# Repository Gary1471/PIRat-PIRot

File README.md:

# PIRat & PIRot

Cílem práce je vytvořit funkční prototyp zařízení PIRat a PIRot. PIRat (vysílač) detekuje pomocí PIR senzoru pohyb člověka/zvířete a pošle bezdrátový signál pomocí ESP-NOW zařízení PIRot (přijímač), který zahlásí upozornění o pohybu. PIRat bude mít dva módy, první „skrytý mód“ jen posílá upozornění na PIRot, druhý „normální mód“ pošle upozornění a zároveň sám PIRat upozorní zvukovým znamením. To umožňuje používat zařízení PIRat samostatně bez zařízení PIRot. PIRot bude mít též dva módy, první „skrytý mód“ upozorní uživatele světelným znamením, druhý „normální mód“ upozorní uživatele světelným i zvukovým znamením.

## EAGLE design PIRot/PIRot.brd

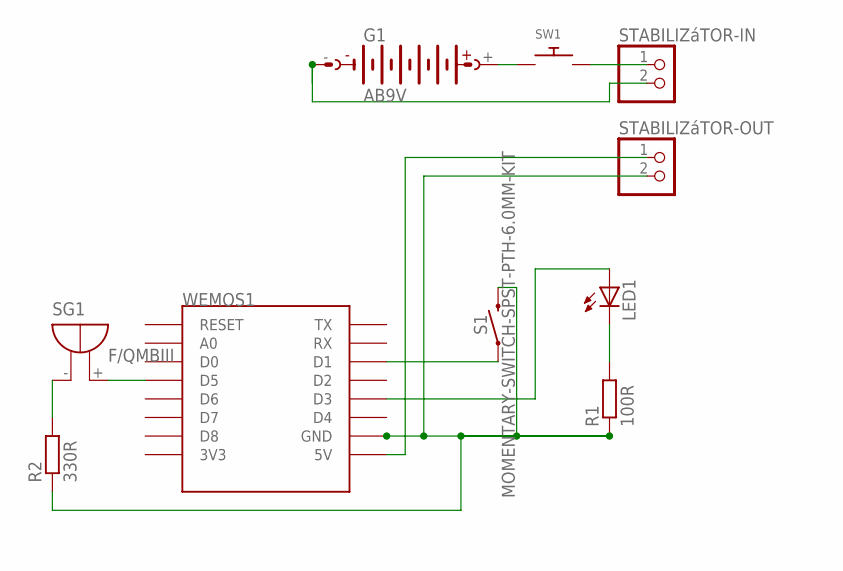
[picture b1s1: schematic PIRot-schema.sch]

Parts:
G1: AB9V
LED1: LED3MM
R1: 100R; 0207/10
R2: 330R; 0207/10
S1: MOMENTARY-SWITCH-SPST-PTH-6.0MM-KIT; TACTILE_SWITCH_PTH_6.0MM_KIT
SG1: F/QMBIII
STABILIZáTOR-IN: PINHD-1X2; 1X02
STABILIZáTOR-OUT: PINHD-1X2; 1X02
SW1: SWITCH_PUSHBUTTONEVQ-PE; TACT_PANA-EVQ
WEMOS1: WEMOS-D1-MINI

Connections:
GND: R1.1, R2.1, S1.3 (2), STABILIZáTOR-OUT.2, WEMOS1.GND
unnamed: LED1.A, WEMOS1.D3
unnamed: LED1.K (C), R1.2
unnamed: G1.+, SW1.P$1
unnamed: STABILIZáTOR-OUT.1, WEMOS1.5V
unnamed: SG1.+ (-), WEMOS1.D5
unnamed: R2.2, SG1.- (+)
unnamed: S1.1, WEMOS1.D1
unnamed: G1.-, STABILIZáTOR-IN.2
unnamed: STABILIZáTOR-IN.1, SW1.P$2

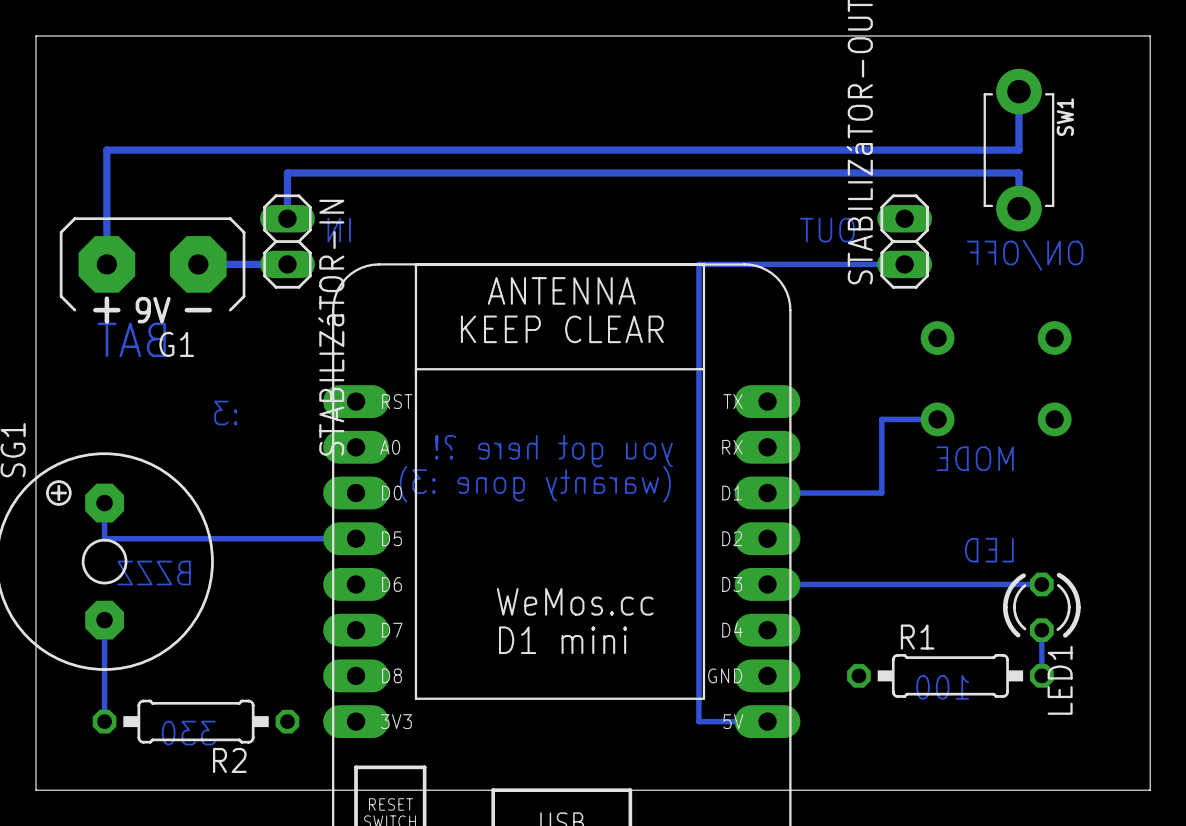
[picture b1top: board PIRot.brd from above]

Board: 2 copper layers, 61.9 x 41.9 mm, 10 parts (1 on the bottom side), 10 nets.

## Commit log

2024-09-20 GLWT
2024-09-20 README
2025-01-05 codes+schemas
2025-03-03 PIRot
2025-03-17 Cleanup
2025-03-17 CLEANUP2
2025-03-17 Update LICENSE

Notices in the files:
parts and their libraries:
SparkFun-Switches: Licensing: Creative Commons ShareAlike 4.0 International - https://creativecommons.org/licenses/by-sa/4.0
